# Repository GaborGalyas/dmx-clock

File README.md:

# DMX controlled Clock
The files here are for making your own DMX controlled clock. Board files, schematics, and source codes can be found here.
# File descriptions:
## 2pix.brd
Printed Circuit Board file created with EAGLE 6.5.0
## 2pix.sch
Schematic file created with EAGLE 6.5.0
## 2pix_top_bom and 2pix_top_cpl 
Bill Of Material and component files what you can upload to a PCB manufacturing site to have your boards assembled
## GGL-CLOCK-FRAME.stl
A 3D printable frame for 2 modules. You need to round the corners of the pcb-s to fit in the corners of the frame. Add a plexiglass to the front with a sheet of frost paper or parchment paper / baking paper between the two. Use M3 bolts from the front to fix the plexi/frost/frame/pcb sandwich together.
## clock_gerbers.zip
Upload this file to a pcb manufacturer site like JLCPCB to have your boards made.
## ggl_clock_dmx_2col.ino
This code is written for an arduino mini with wired dmx input. 
This will need tinkering, you need to connect the arduino to the modules and implement the dmx receiving circuit.
I will work on making a pcb design for a drop in replacement for the wemos d1 mini.
## wireless_clock_wifimanager_2col.ino
This version is for a wemos D1 mini. After assembling the pcb-s solder the wemos d1 mini to the first module, and upload code. For configuration short the D7 pin to ground on boot, and the wifi manager will load. You will be presented with a wireless hotspot named "GGL ARTNET CLOCK CONFIG ME". After connecting, you can configure the wifi network that has Art-Net data coming from the lighting network, and set the dmx address too. Once saved, on every boot the clock will try to connect to the network you provided.

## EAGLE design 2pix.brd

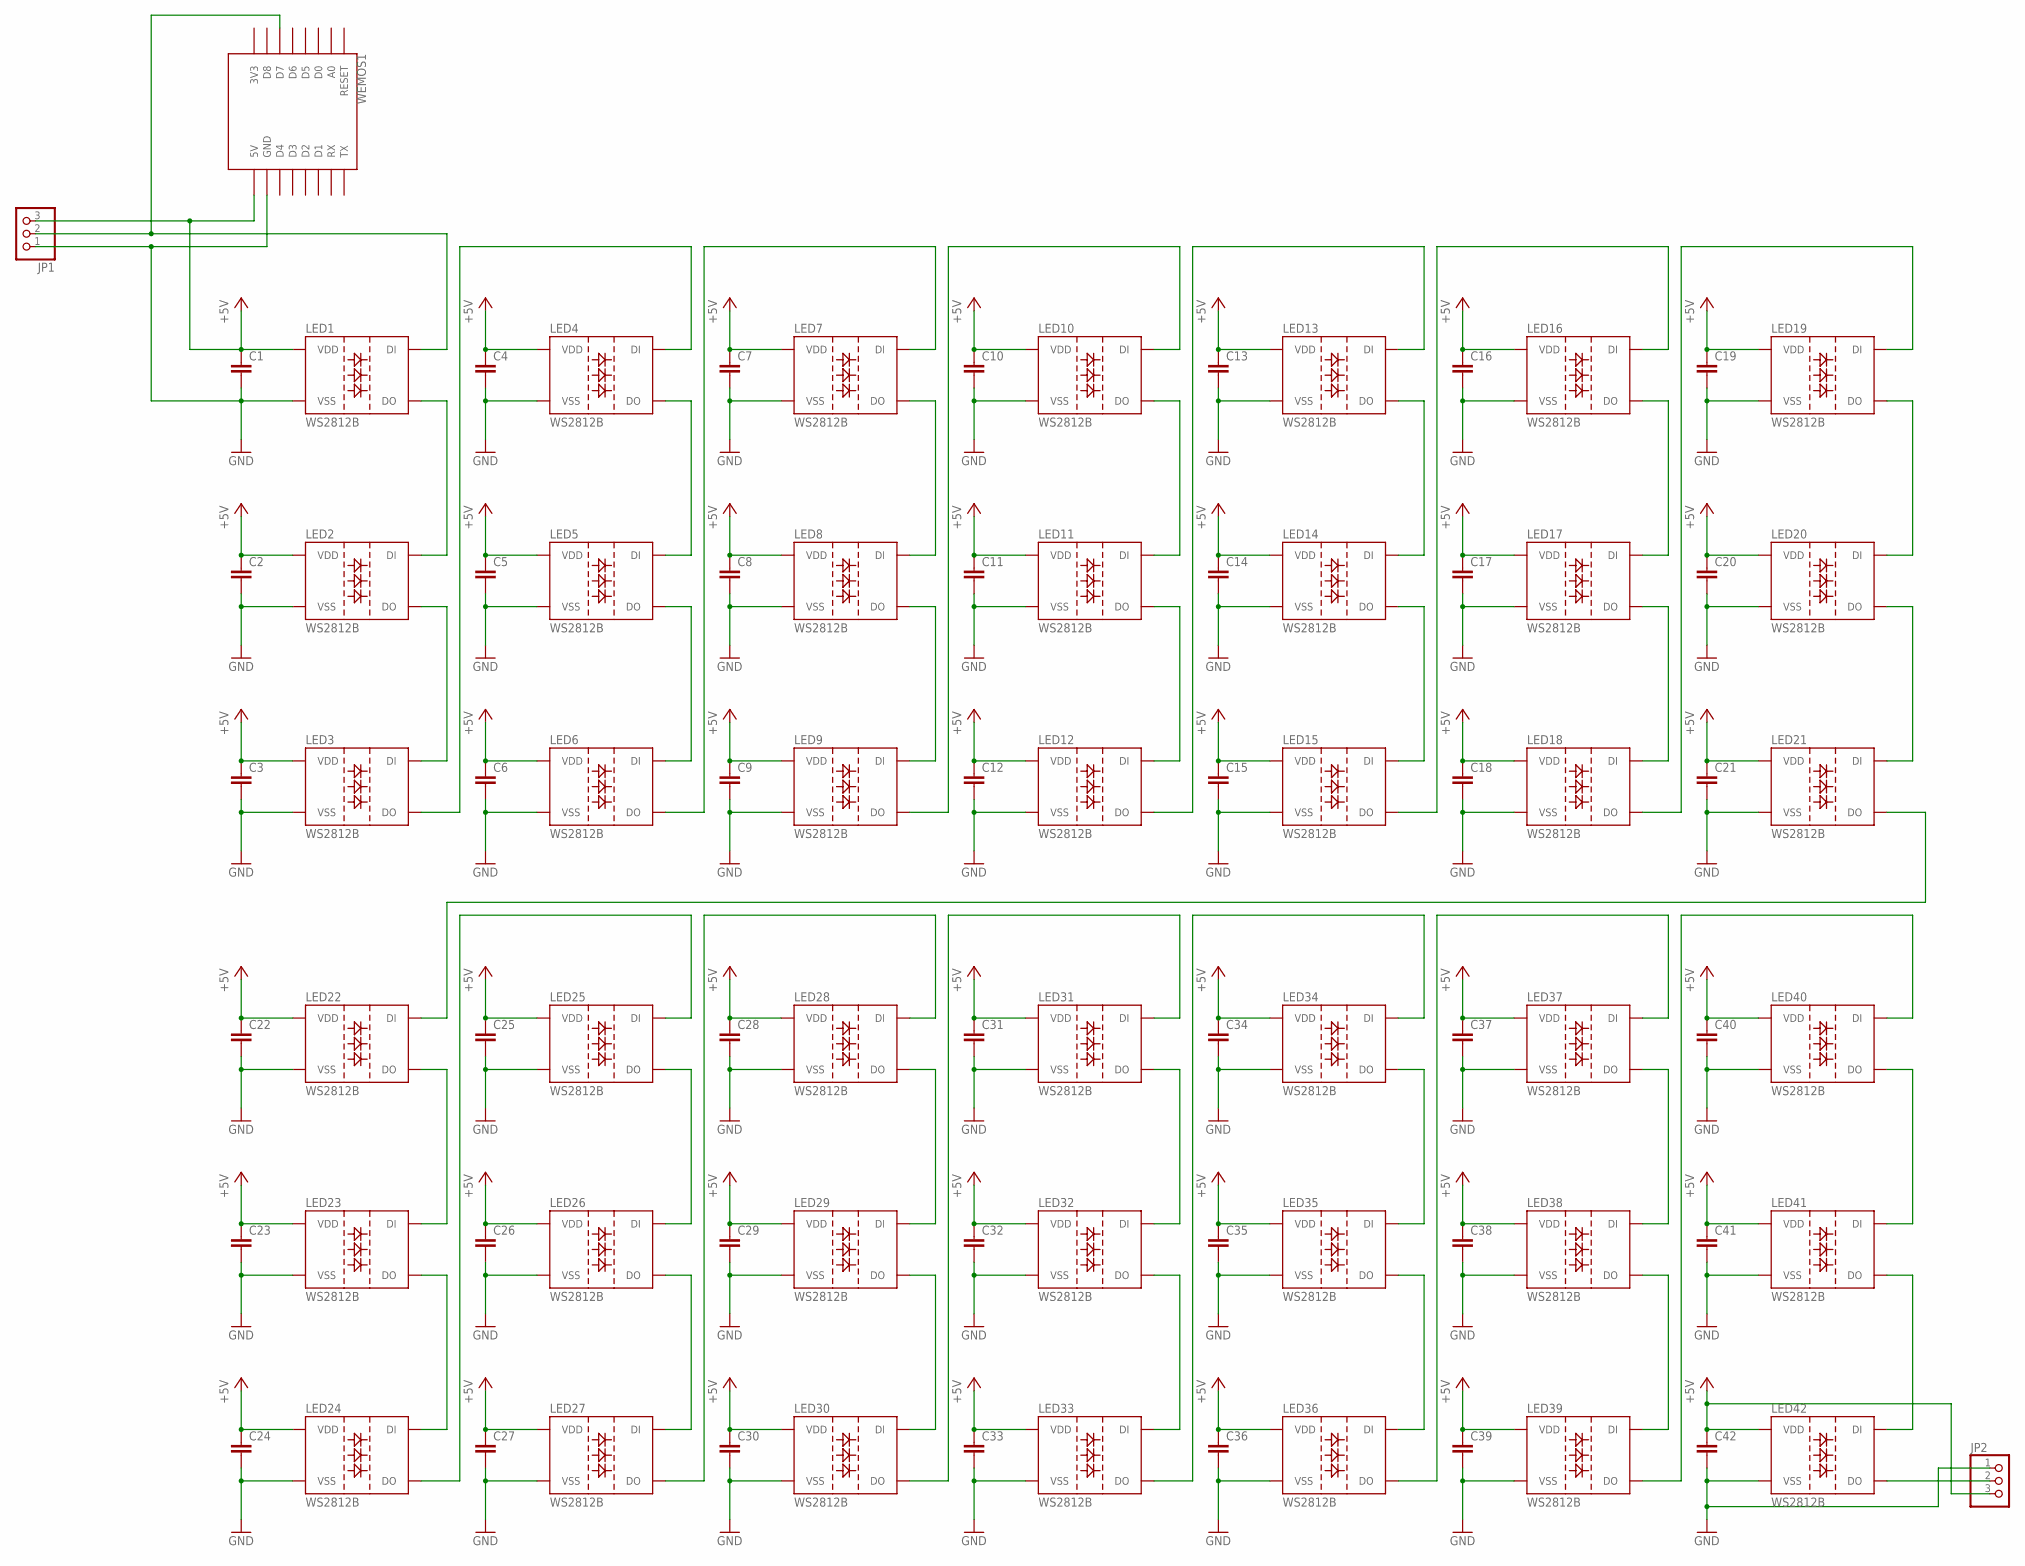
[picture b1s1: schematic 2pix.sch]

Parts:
C1, C2, C3, C4, C5, C6, C7, C8, C9, C10, C11, C12, C13, C14, C15, C16, C17, C18, C19, C20, C21, C22, C23, C24, C25, C26, C27, C28, C29, C30, C31, C32, C33, C34, C35, C36, C37, C38, C39, C40, C41, C42: C-EUC1206; C1206
JP1, JP2: PINHD-1X3; 1X03
LED1, LED2, LED3, LED4, LED5, LED6, LED7, LED8, LED9, LED10, LED11, LED12, LED13, LED14, LED15, LED16, LED17, LED18, LED19, LED20, LED21, LED22, LED23, LED24, LED25, LED26, LED27, LED28, LED29, LED30, LED31, LED32, LED33, LED34, LED35, LED36, LED37, LED38, LED39, LED40, LED41, LED42: WS2812B
WEMOS1: WEMOS-D1-MINI

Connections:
+5V: C1.1, C2.1, C3.1, C4.1, C5.1, C6.1, C7.1, C8.1, C9.1, C10.1, C11.1, C12.1, C13.1, C14.1, C15.1, C16.1, C17.1, C18.1, C19.1, C20.1, C21.1, C22.1, C23.1, C24.1, C25.1, C26.1, C27.1, C28.1, C29.1, C30.1, C31.1, C32.1, C33.1, C34.1, C35.1, C36.1, C37.1, C38.1, C39.1, C40.1, C41.1, C42.1, JP1.3, JP2.3, LED1.1 (VDD), LED2.1 (VDD), LED3.1 (VDD), LED4.1 (VDD), LED5.1 (VDD), LED6.1 (VDD), LED7.1 (VDD), LED8.1 (VDD), LED9.1 (VDD), LED10.1 (VDD), LED11.1 (VDD), LED12.1 (VDD), LED13.1 (VDD), LED14.1 (VDD), LED15.1 (VDD), LED16.1 (VDD), LED17.1 (VDD), LED18.1 (VDD), LED19.1 (VDD), LED20.1 (VDD), LED21.1 (VDD), LED22.1 (VDD), LED23.1 (VDD), LED24.1 (VDD), LED25.1 (VDD), LED26.1 (VDD), LED27.1 (VDD), LED28.1 (VDD), LED29.1 (VDD), LED30.1 (VDD), LED31.1 (VDD), LED32.1 (VDD), LED33.1 (VDD), LED34.1 (VDD), LED35.1 (VDD), LED36.1 (VDD), LED37.1 (VDD), LED38.1 (VDD), LED39.1 (VDD), LED40.1 (VDD), LED41.1 (VDD), LED42.1 (VDD), WEMOS1.5V
GND: C1.2, C2.2, C3.2, C4.2, C5.2, C6.2, C7.2, C8.2, C9.2, C10.2, C11.2, C12.2, C13.2, C14.2, C15.2, C16.2, C17.2, C18.2, C19.2, C20.2, C21.2, C22.2, C23.2, C24.2, C25.2, C26.2, C27.2, C28.2, C29.2, C30.2, C31.2, C32.2, C33.2, C34.2, C35.2, C36.2, C37.2, C38.2, C39.2, C40.2, C41.2, C42.2, JP1.1, JP2.1, LED1.3 (VSS), LED2.3 (VSS), LED3.3 (VSS), LED4.3 (VSS), LED5.3 (VSS), LED6.3 (VSS), LED7.3 (VSS), LED8.3 (VSS), LED9.3 (VSS), LED10.3 (VSS), LED11.3 (VSS), LED12.3 (VSS), LED13.3 (VSS), LED14.3 (VSS), LED15.3 (VSS), LED16.3 (VSS), LED17.3 (VSS), LED18.3 (VSS), LED19.3 (VSS), LED20.3 (VSS), LED21.3 (VSS), LED22.3 (VSS), LED23.3 (VSS), LED24.3 (VSS), LED25.3 (VSS), LED26.3 (VSS), LED27.3 (VSS), LED28.3 (VSS), LED29.3 (VSS), LED30.3 (VSS), LED31.3 (VSS), LED32.3 (VSS), LED33.3 (VSS), LED34.3 (VSS), LED35.3 (VSS), LED36.3 (VSS), LED37.3 (VSS), LED38.3 (VSS), LED39.3 (VSS), LED40.3 (VSS), LED41.3 (VSS), LED42.3 (VSS), WEMOS1.GND
unnamed: LED4.2 (DO), LED5.4 (DI)
unnamed: LED1.2 (DO), LED2.4 (DI)
unnamed: LED3.2 (DO), LED4.4 (DI)
unnamed: LED2.2 (DO), LED3.4 (DI)
unnamed: LED5.2 (DO), LED6.4 (DI)
unnamed: LED6.2 (DO), LED7.4 (DI)
unnamed: LED7.2 (DO), LED8.4 (DI)
unnamed: LED9.2 (DO), LED10.4 (DI)
unnamed: LED8.2 (DO), LED9.4 (DI)
unnamed: LED10.2 (DO), LED11.4 (DI)
unnamed: LED11.2 (DO), LED12.4 (DI)
unnamed: LED12.2 (DO), LED13.4 (DI)
unnamed: LED13.2 (DO), LED14.4 (DI)
unnamed: LED15.2 (DO), LED16.4 (DI)
unnamed: LED14.2 (DO), LED15.4 (DI)
unnamed: LED16.2 (DO), LED17.4 (DI)
unnamed: LED17.2 (DO), LED18.4 (DI)
unnamed: LED18.2 (DO), LED19.4 (DI)
unnamed: LED19.2 (DO), LED20.4 (DI)
unnamed: LED21.2 (DO), LED22.4 (DI)
unnamed: LED20.2 (DO), LED21.4 (DI)
unnamed: LED22.2 (DO), LED23.4 (DI)
unnamed: LED24.2 (DO), LED25.4 (DI)
unnamed: LED23.2 (DO), LED24.4 (DI)
unnamed: LED25.2 (DO), LED26.4 (DI)
unnamed: LED26.2 (DO), LED27.4 (DI)
unnamed: LED27.2 (DO), LED28.4 (DI)
unnamed: LED28.2 (DO), LED29.4 (DI)
unnamed: LED30.2 (DO), LED31.4 (DI)
unnamed: LED29.2 (DO), LED30.4 (DI)
unnamed: LED31.2 (DO), LED32.4 (DI)
unnamed: LED32.2 (DO), LED33.4 (DI)
unnamed: LED33.2 (DO), LED34.4 (DI)
unnamed: LED34.2 (DO), LED35.4 (DI)
unnamed: LED36.2 (DO), LED37.4 (DI)
unnamed: LED35.2 (DO), LED36.4 (DI)
unnamed: LED37.2 (DO), LED38.4 (DI)
unnamed: LED38.2 (DO), LED39.4 (DI)
unnamed: LED39.2 (DO), LED40.4 (DI)
unnamed: LED40.2 (DO), LED41.4 (DI)
unnamed: JP1.2, LED1.4 (DI), WEMOS1.D7
unnamed: LED41.2 (DO), LED42.4 (DI)
unnamed: JP2.2, LED42.2 (DO)

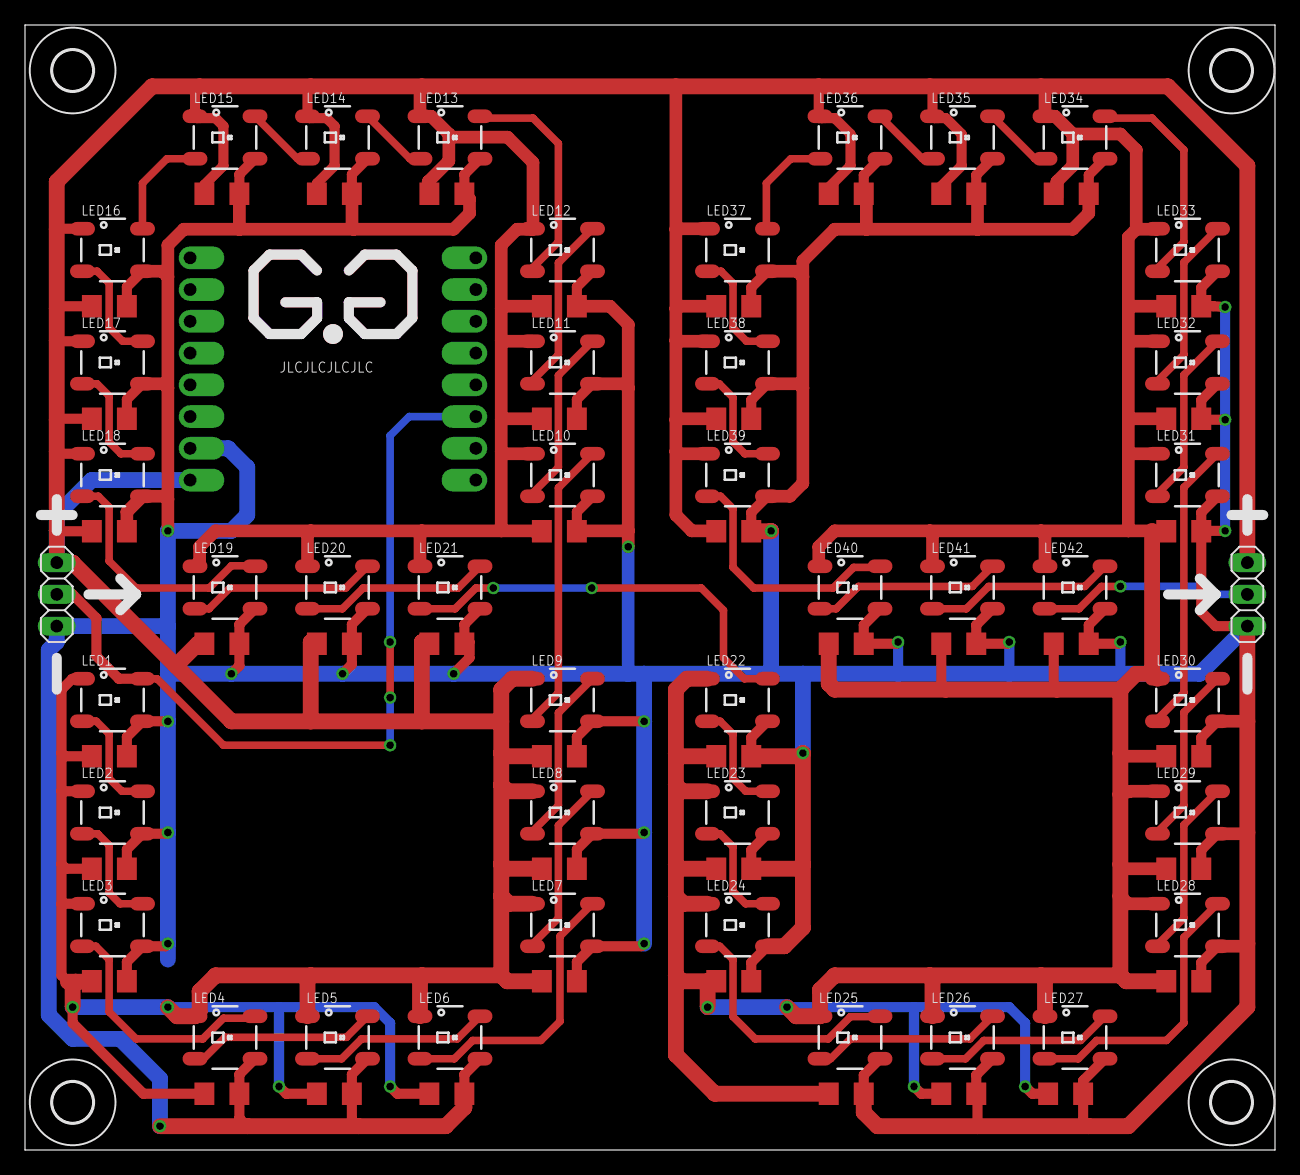
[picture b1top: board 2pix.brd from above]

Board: 2 copper layers, 100.0 x 90.0 mm, 91 parts (1 on the bottom side), 45 nets.

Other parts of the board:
U$1, U$2, U$3, U$4: 3,2

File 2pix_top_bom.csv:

Comment,Designator,Footprint,LCSC Part #
,C1 C2 C3 C4 C5 C6 C7 C8 C9 C10 C11 C12 C13 C14 C15 C16 C17 C18 C19 C20 C21 C22 C23 C24 C25 C26 C27 C28 C29 C30 C31 C32 C33 C34 C35 C36 C37 C38 C39 C40 C41 C42,C1206,
WS2812B,LED1 LED2 LED3 LED4 LED5 LED6 LED7 LED8 LED9 LED10 LED11 LED12 LED13 LED14 LED15 LED16 LED17 LED18 LED19 LED20 LED21 LED22 LED23 LED24 LED25 LED26 LED27 LED28 LED29 LED30 LED31 LED32 LED33 LED34 LED35 LED36 LED37 LED38 LED39 LED40 LED41 LED42,WS2812B,

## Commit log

2023-02-25 Found the pcb files
